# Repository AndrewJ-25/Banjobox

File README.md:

# Banjobox

Banjobox is a banjo case with a built in tuner and temperature/ humidity sensor. I designed it to store a mountain banjo I made but the case can be modified to accomodate other string instruments.

Purchasing a banjo case is difficult, especially as shape varies a lot. Banjobox is low cost (plywood, softwood timber) and super customiseable!

Banjobox features a Seeed Studios Xiao RP2040 running MicroPython. UI consists of a rotary encoder and 0.91" OLED display. You can select different notes to be played through the speaker to tune your banjo.

Pressing the rotary encoder button switches between monitor mode and tune mode. Monitor mode displays temperature and humidity readings. Tune mode plays a square wave. Turning the knob changes the note played.

Files for 3D printing and laser cutting can be found in the OnShape project linked below.

### Demo
https://www.youtube.com/watch?v=Ie8TWf3fN2Y

### Features
 - Seeed Studios Xiao RP2040
 - SHT31 temp + humidity sensor
 - PAM8302 Class-D amp with 3W 4ohm speaker
 - Powered by 3x AA batteries
 - 0.91 inch OLED display
 - EC11 rotary encoder

## OnShape project
https://cad.onshape.com/documents/49037cb32e4fd0c851c4d81b/w/99bbea41b70cb909ece41dd4/e/4da4cdf8e8884e6941d1b422?renderMode=0&uiState=69cc3025f9c68d0f90eed99a

## Schematic

## Case construction tips
Construction of the case requires minimal woodworking skills and tools. I reccomend using some wood screws rather than relying on glue alone. A full set of plans can be found in the production folder.

### General
 - Add felt padding where appropriate (including this in the CAD model was impractical). The green blocks on the lid can be made by wrapping foam with felt.

 - Heel supports can be reinforced with metal brackets or dowels
 - Remember to cut holes to run wires!
 - Hold battery holder in place with velcro.
 - SHT31 breakout board to be fixed inside battery compartment with sticky foam. Speaker vents will ensure good airflow.
 - Electronics parts are held in place by two acrylic covers. Use long M3 bolts or threaded rod to mount the PCB.

### 3D printing
 - The PCB cover and speaker/ battery cover are each supported by three 3D printed columns
 - Use M3 heatset inserts
 - Glue in place

### Laser cutting
 - Laser cut PCB and spekeaker/ battery covers from clear acrylic
 - Recommended 4mm but exact thickness is unimportant

Remember to cut wire holes in the side supports! See below:

### Note regarding PCB
- In the final product, the external voltage regulator and accompanying capacitors were omitted in favour of the XIAO's onboard voltage regulator.

## Images

## BOM
NOTE: Links are suggestions only. Some parts are ubiquitous and purchasing online would be impractical not to mention expensive. I'm from the UK hence some links might not work if you live overseas. Prices may vary.
| Quantity | Item                          | Cost/£ | Link |
|----------|-------------------------------|--------|--------|
| 1        | Seeed Studios Xiao RP2040     | 3.90   | https://thepihut.com/products/seeed-xiao-rp2040 |
| 1        | PCB                           | 5.00      | https://jlcpcb.com/ |
| 1        | 0.91 inch OLED               | 3.80   | https://www.aliexpress.com/item/1005006365845676.html |
| 1        | SHT31 breakout board         | 1.57   | https://www.aliexpress.com/item/32695064184.html |
| -        | Components                    | 10.00      | https://www.digikey.co.uk/ |
| 1        | 3W speaker                   | 3.40   | https://thepihut.com/products/mono-enclosed-speaker-3w-4-ohm |
| 1        | Toggle switch                | 1.67   | https://www.digikey.co.uk/en/products/detail/cit-relay-and-switch/ANT11SEBQE/12503360 |
| 1        | 3xAA battery holder          | 1.99   | https://www.ebay.co.uk/itm/358406972409?_skw=3+x+aa+battery+holder |
| 6        | 3D printed parts             | 2.00      | https://jlcpcb.com/ |
| 2        | laser-cut acrylic            | 0.50      | https://jlcpcb.com/ |
| 6        | Heatset insert               | 2.89   | https://www.ebay.co.uk/itm/314297471901 |
| 13       | M3 screw                     | 7.59   | https://www.ebay.co.uk/itm/305743217020 |
| 7        | M3 nut                       | 3.38   | https://www.ebay.co.uk/itm/167673257973 |
| -        | Wood screws                  | 7.74      | https://www.ebay.co.uk/itm/277661008745?_skw=wood+screws |
| -        | 15mm timber      | 16.00      | https://www.homedepot.com/p/Waddell-Project-Board-24-in-x-4-in-x-0-5-in-Unfinished-S4S-Poplar-Hardwood-w-No-Finger-Joints-Ideal-for-DIY-Shelving-PB19418/329189316 |
| 1        | Plywood 9mm                  | 30.00  | https://www.ebay.co.uk/itm/257438787345?_skw=9mm+plywood |
| 2        | Hinges                       | 1.97   | https://www.ebay.co.uk/itm/222426341432 |
| 2        | Hook and latch               | 3.60   | https://www.ebay.co.uk/itm/168179187930 |
| 1        | Handle                       | 4.20   | https://www.ebay.co.uk/itm/306436283287 |
| 11       | Rubber feet                  | 3.29   | https://www.ebay.co.uk/itm/173200464234 |
| -        | Foam padding                 | 10.99  | https://www.ebay.co.uk/itm/112490209816 |
| -        | Felt padding                 | 6.25   | https://www.ebay.co.uk/itm/188091406494 |
|TOTAL:    |                              | 131.73 | |

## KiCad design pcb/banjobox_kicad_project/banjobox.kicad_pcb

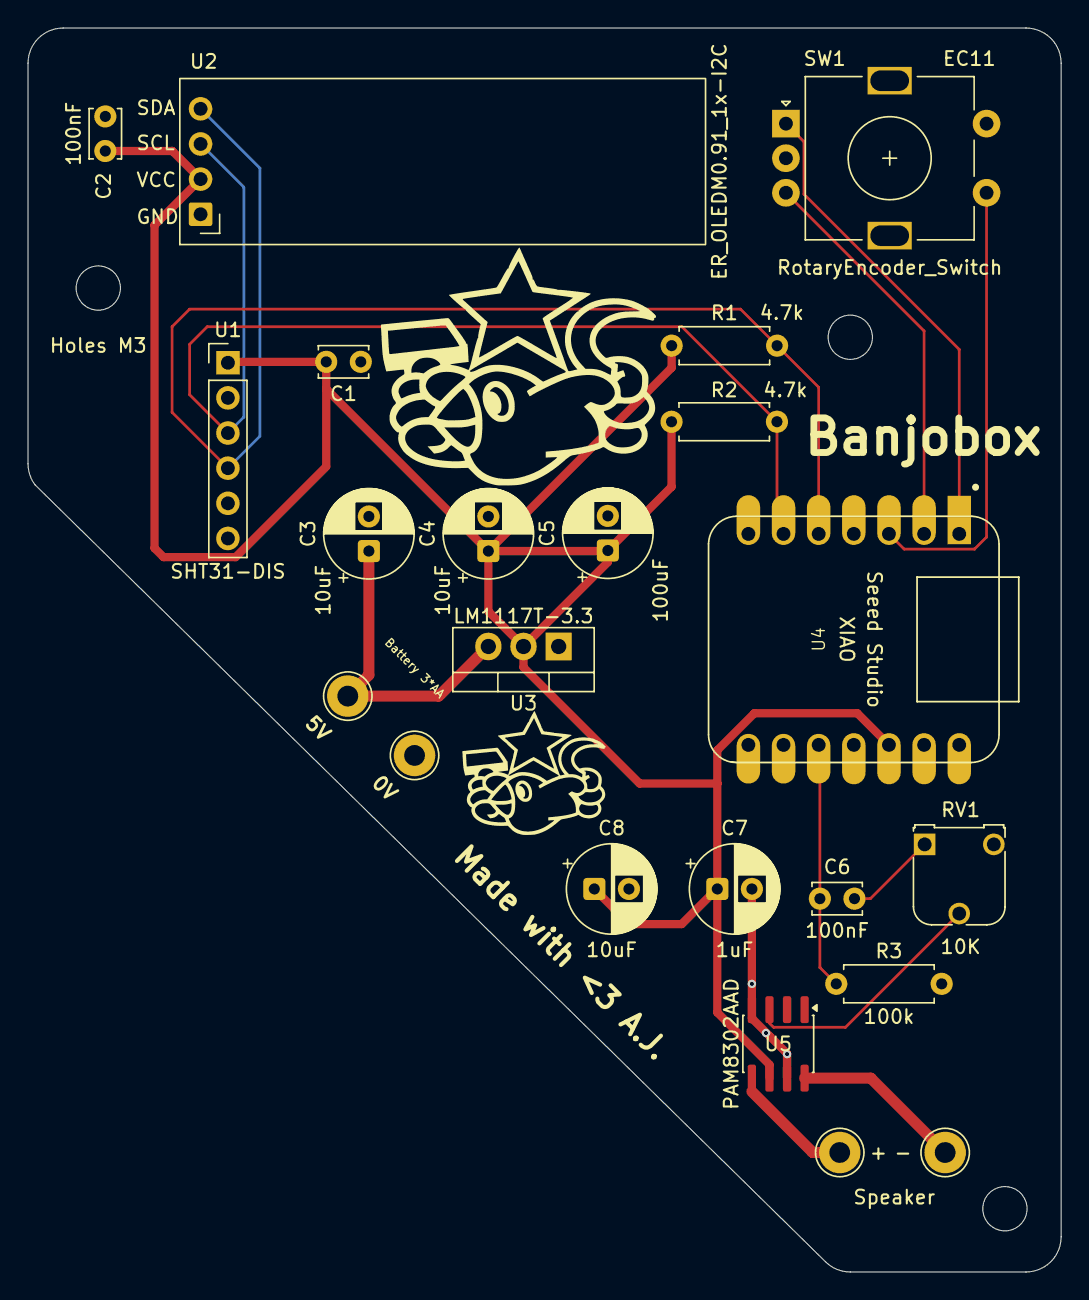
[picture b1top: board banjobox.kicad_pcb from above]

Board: 2 copper layers, 74.7 x 89.9 mm, 22 parts (0 on the bottom side), 13 nets.

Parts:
C1, C2, C6: 100nF; C_Disc_D3.4mm_W2.1mm_P2.50mm
C3, C4, C8: 10uF; CP_Radial_D6.3mm_P2.50mm
C5: 100uF; CP_Radial_D6.3mm_P2.50mm
C7: 1uF; CP_Radial_D6.3mm_P2.50mm
R1, R2: 4.7k; R_Axial_DIN0207_L6.3mm_D2.5mm_P7.62mm_Horizontal
R3: 100k; R_Axial_DIN0207_L6.3mm_D2.5mm_P7.62mm_Horizontal
RV1: 10K; Potentiometer_Runtron_RM-065_Vertical
SW1: RotaryEncoder_Switch; RotaryEncoder_Alps_EC11E-Switch_Vertical_H20mm
TP1, TP2, TP3, TP4: TestPoint; TestPoint_THTPad_D3.0mm_Drill1.5mm
U1: SHT31-DIS; PinHeader_1x06_P2.54mm_Vertical
U2: ER_OLEDM0.91_1x-I2C
U3: LM1117T-3.3; TO-220-3_Vertical
U4: MOUDLE-SEEEDUINO-XIAO; XIAO-Generic-Hybrid-14P-2.54-21X17.8MM
U5: PAM8302AAD; SOIC-8_3.9x4.9mm_P1.27mm

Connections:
+BATT: C3.1, TP1.1 (1_1), U3.3 (VI)
-BATT: C1.1, C2.1, C3.2, C4.2, C5.2, C7.2, C8.2, R3.2, RV1.3, SW1.C, SW1.S2, TP2.1 (1_1), U1.2 (VSS), U1.5 (ADDR), U2.1 (GND), U3.1 (GND), U4.13 (GND), U5.4 (IN-), U5.7 (GND)
EC11A: SW1.A, U4.1 (PA02_A0_D0)
EC11B: SW1.B, U4.2 (PA4_A1_D1)
EC11SW1: SW1.S1, U4.3 (PA10_A2_D2)
unnamed: C6.2, RV1.1
unnamed: RV1.2, U5.3 (IN+)
unnamed: TP3.1 (1_1), U5.5 (OUT+)
unnamed: TP4.1 (1_1), U5.8 (OUT-)
PWM: C6.1, R3.1, U4.10 (PA5_A9_D9_MISO)
SCL: R2.1, U1.3 (SCL), U2.3 (SCL), U4.6 (PA9_A5_D5_SCL)
SDA: R1.2, U1.4 (SDA), U2.4 (SDA), U4.5 (PA8_A4_D4_SDA)
VCC: C1.2, C2.2, C4.1, C5.1, C7.1, C8.1, R1.1, R2.2, U1.1 (VDD), U2.2 (VCC), U3.2 (VO), U4.12 (3V3), U5.6 (VDD)

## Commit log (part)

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2026-03-31 added production folder
2026-04-01 started drawing schematic
2026-04-02 first draft of schematic
2026-04-03 uploaded pcb workflow, copied from chatgpt. made minor change to schematic.
2026-04-04 completed drawing schematic
2026-04-04 rearranged files
2026-04-06 added voltage regulator to schematic and finished assigning footprints
2026-04-08 removed R pin from SHT31 to better suit breakout board
2026-04-08 assigned new footprints (pinheader) and more progress on pcb
2026-04-09 routed pcb
2026-04-09 forgot to save after last commit, routed pcb
2026-04-15 added bird graphic to pcb and added some silkscreen labels
2026-04-15 pcb added all silkscreen text
2026-04-16 updated 3d models for pcb footprints
2026-04-18 created pycharm project for writing firmware
2026-04-19 started outline of code
2026-04-21 implemented encoder logic
2026-04-22 completed first iteration of code
2026-04-25 created BOM
2026-04-30 downloaded zine
2026-04-30 added images
2026-04-30 images?
2026-04-30 more image:)
2026-04-30 downloaded plans
2026-04-30 organised images
2026-04-30 deleted code folder uneeded
2026-04-30 wire route
2026-05-01 uploaded step and dxf files to production
2026-05-02 added gitignore
2026-05-04 re added bom
2026-05-04 removed tracking for backups etc
2026-05-04 removed .idea from version control
2026-05-06 converted zine to pdf
2026-05-20 exported edited cad models
2026-05-20 file organisation
